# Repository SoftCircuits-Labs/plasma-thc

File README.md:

# plasma-thc
A fully isolated Plasma THC which an be used with any CNC control system which accepts torch Up and Down signals, eg. MACH 3, LinuxCNC, CNConv, Planet CNC etc

The Plasma THC has 2 parts - PTHC-Driver (controller unit) and the PTHC-Probe (for voltage sensing), which are connected via an optical cable.
- PTHC-Probe is installed close to the plasma source. It connects to plasma voltage and runs from a 12VDC supply (provided with the device).
- PTHC-Driver unit is installed closer to the CNC controller. It gives signal to the CNC controller for torch UP, DOWN and ARC OK. It operates via a 12VDC supply (provided with the device)
- These 2 modules are connected via an optical cable which suppresses any high voltage electrical interference, EMI, spikes etc, which are very common in plasma CNC and can damage the
plasma CNC.

Link to user's manual - https://de60002c-e075-4620-9e75-7ffce0da00f8.usrfiles.com/ugd/de6000_ddb20201a9d644779807a9140060d1e7.pdf

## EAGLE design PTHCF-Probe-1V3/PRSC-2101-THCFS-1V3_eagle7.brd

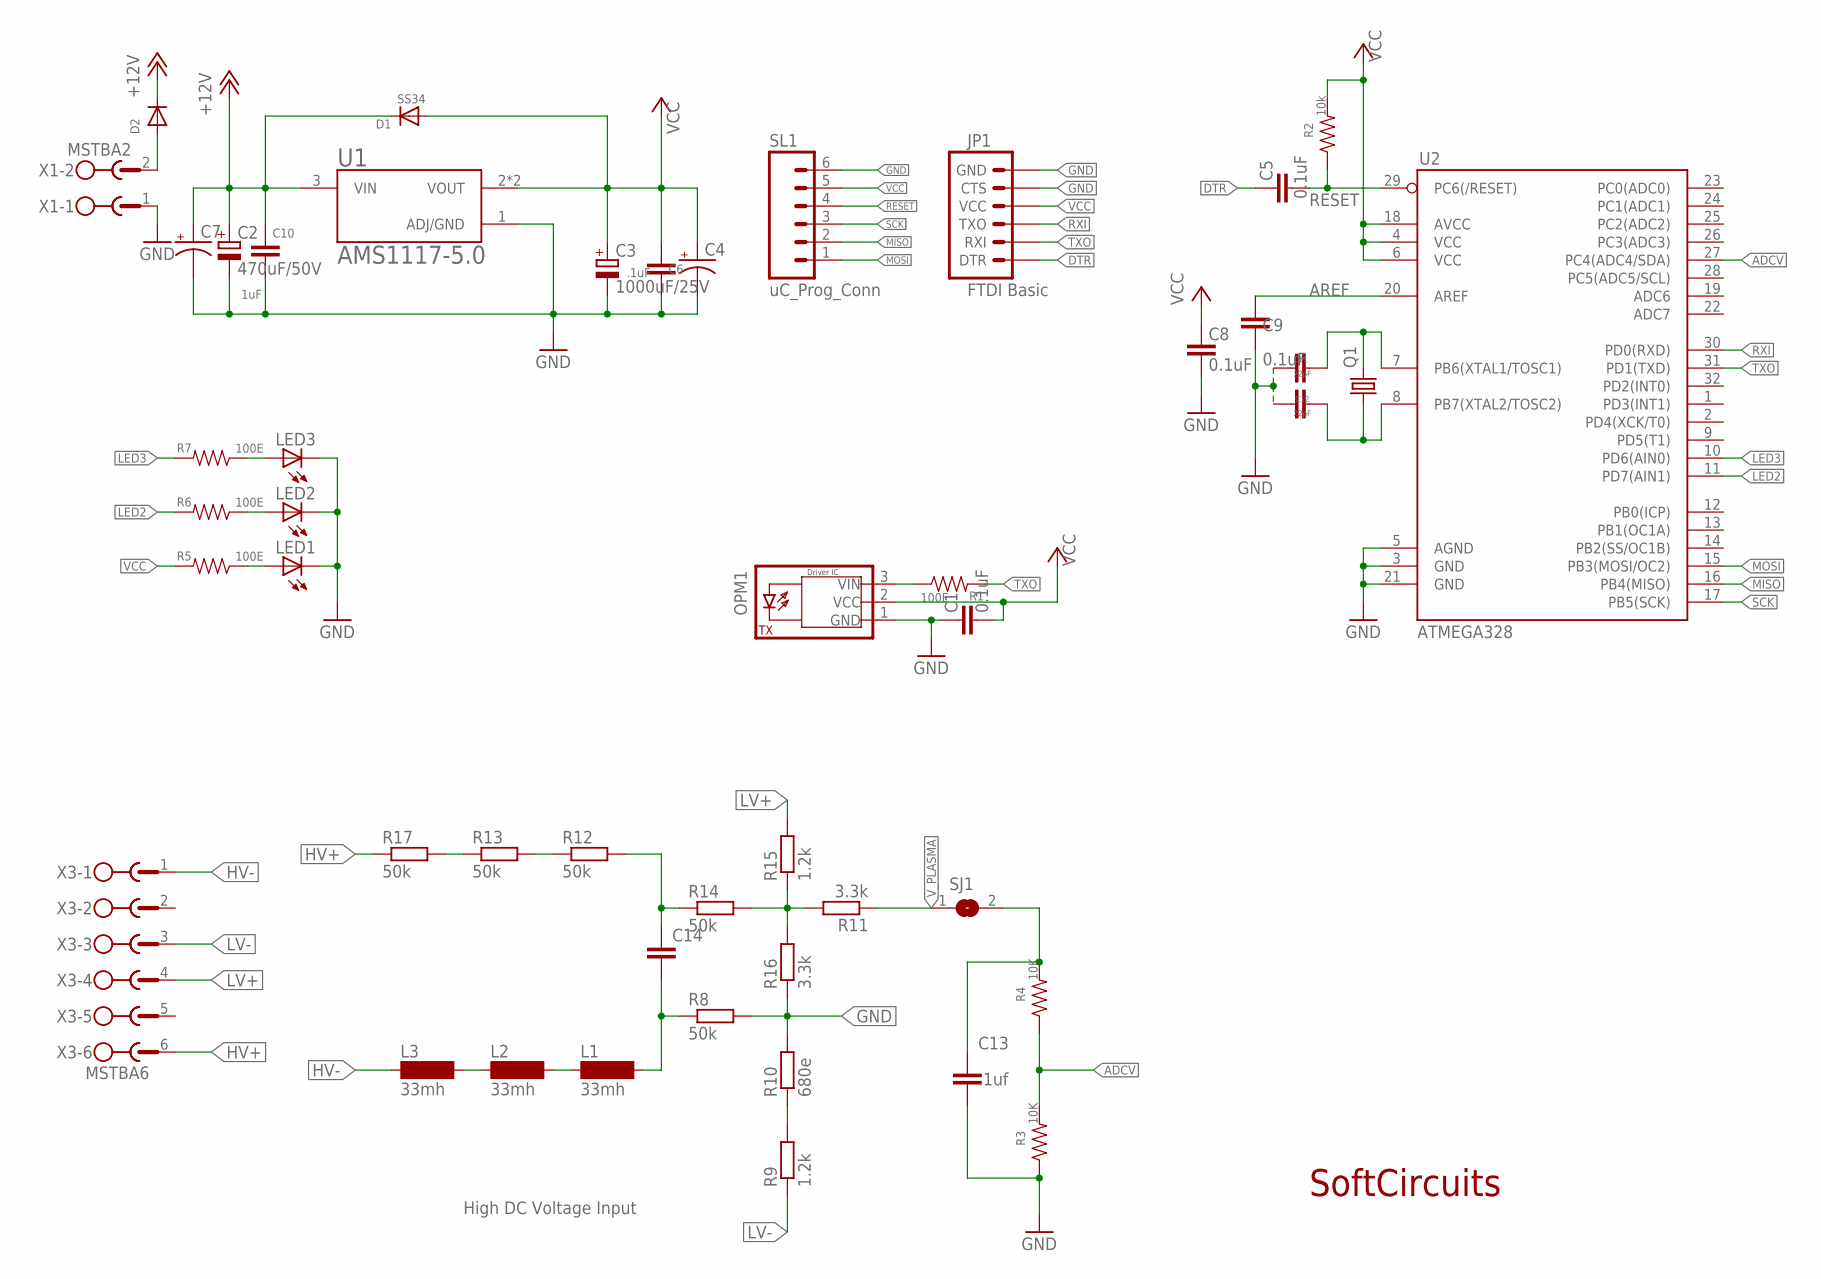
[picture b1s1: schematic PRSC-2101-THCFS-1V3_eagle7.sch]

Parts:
C1, C5, C8, C9: 0.1uF; C1206
C2: 470uF/50V; 153CLV-1010
C3: 1000uF/25V; 153CLV-1010
C4, C7: CAP_POL3528-KIT; EIA3528-KIT
C6: .1uF; C1206
C10: 1uF; C1206
C11, C12: 22pF; C1206
C13: .1uf; C1206
C14: C-EU050-025X075; C050-025X075
D1: SS34; SMADIODE
D2: DIODESMA; SMADIODE
JP1: FTDI Basic; 1X06
L1, L2, L3: 33mh; MY_INDUCTOR
LED1, LED2, LED3: LED3MM
OPM1: TOSLINK_DQT-025; TOSLINK_DQ-025
Q1: CRYSTALHC49UP; HC49UP
R1, R5, R6, R7: 100E; 1206
R2: 10k; 1206
R3, R4: 10K; 1206
R8, R12, R13, R14, R17: 50k; 0207/5V
R9, R15: 1.2k; 0207/2V
R10: 680e; 0207/5V
R11: 3.3k; 0207/2V
R16: 3.3k; 0207/15
SJ1: SJ
SL1: uC_Prog_Conn; 06P
U1: AMS1117-5.0; SOT229P700X180-4N
U2: ATMEGA328; TQFP32-08
X1: MSTBA2
X3: MSTBA6

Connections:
+12V: C2.+, C7.A (+), C10.1, D1.C, D2.C, U1.3 (VIN)
ADCV: R3.2, R4.1, U2.27 (PC4(ADC4/SDA))
AREF: C9.2, U2.20 (AREF)
DTR: C5.2, JP1.1 (DTR)
GND: C1.2, C2.-, C3.-, C4.C (-), C6.2, C7.C (-), C8.1, C9.1, C10.2, C11.2, C12.2, C13.2, JP1.5 (CTS), JP1.6 (GND), LED1.K (C), LED2.K (C), LED3.K (C), OPM1.1 (GND), R3.1, R8.2, R10.2, R16.1, SL1.6, U1.1 (ADJ/GND), U2.3 (GND), U2.5 (AGND), U2.21 (GND), X1.1
HV+: R17.1, X3.6
HV-: L3.1, X3.1
LED2: R6.2, U2.11 (PD7(AIN1))
LED3: R7.2, U2.10 (PD6(AIN0))
LV+: R15.2, X3.4
LV-: R9.1, X3.3
MISO: SL1.2, U2.16 (PB4(MISO))
MOSI: SL1.1, U2.15 (PB3(MOSI/OC2))
unnamed: LED3.A, R7.1
unnamed: R13.1, R17.2
unnamed: C14.1, R12.2, R14.1
unnamed: L1.1, L2.2
unnamed: D2.A, X1.2
unnamed: R12.1, R13.2
unnamed: L2.1, L3.2
unnamed: C14.2, L1.2, R8.1
unnamed: OPM1.3 (VIN), R1.1
unnamed: R11.2, R14.2, R15.1, R16.2
unnamed: C11.1, Q1.2, U2.7 (PB6(XTAL1/TOSC1))
unnamed: R9.2, R10.1
unnamed: C12.1, Q1.1, U2.8 (PB7(XTAL2/TOSC2))
unnamed: LED2.A, R6.1
unnamed: LED1.A, R5.1
PLASMA_VIN: C13.1, R4.2, SJ1.2
RESET: C5.1, R2.1, SL1.4, U2.29 (PC6(/RESET))
RXI: JP1.3 (TXO), U2.30 (PD0(RXD))
SCK: SL1.3, U2.17 (PB5(SCK))
TXO: JP1.2 (RXI), R1.2, U2.31 (PD1(TXD))
VCC: C1.1, C3.+, C4.A (+), C6.1, C8.2, D1.A, JP1.4 (VCC), OPM1.2 (VCC), R2.2, R5.2, SL1.5, U1.2 (VOUT), U1.4 (VOUT), U2.4 (VCC), U2.6 (VCC), U2.18 (AVCC)
V_PLASMA: R11.1, SJ1.1

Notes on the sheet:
SoftCircuits
High DC Voltage Input

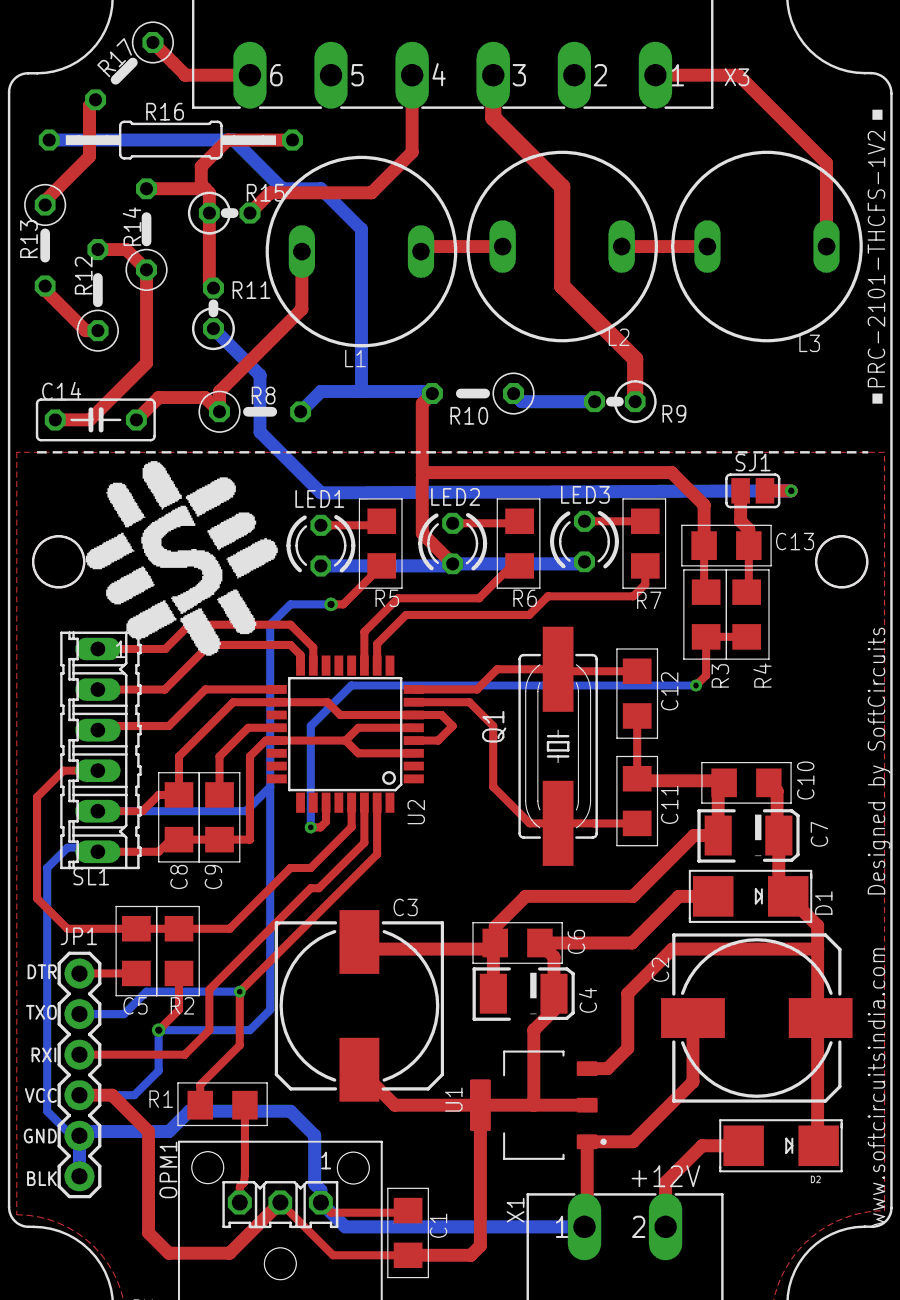
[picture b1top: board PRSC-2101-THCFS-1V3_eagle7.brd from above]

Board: 2 copper layers, 50 parts (1 on the bottom side), 35 nets.

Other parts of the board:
LOGO1, LOGO100: SC_LOGO

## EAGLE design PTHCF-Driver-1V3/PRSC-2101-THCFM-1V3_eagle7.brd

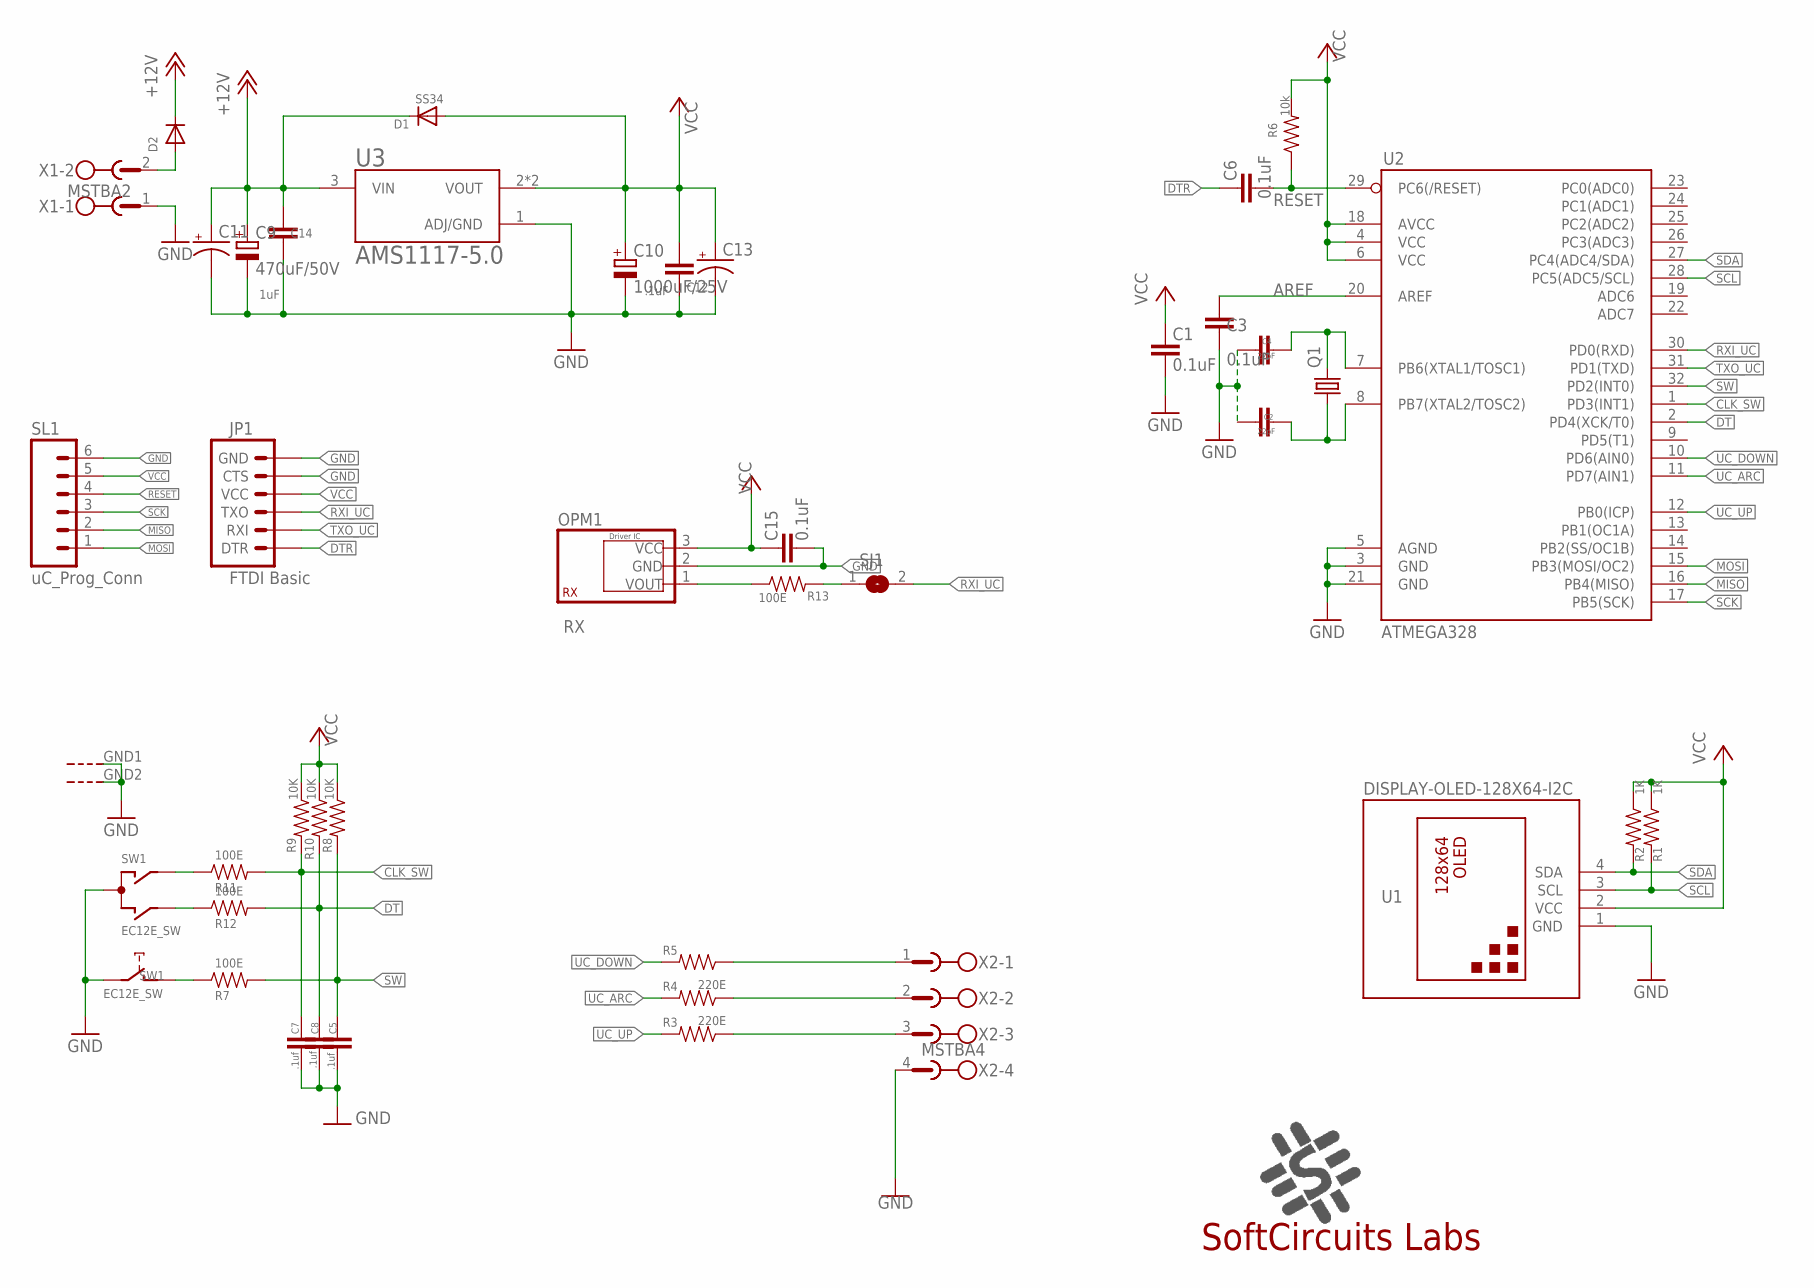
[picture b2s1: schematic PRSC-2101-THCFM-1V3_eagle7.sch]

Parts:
C1, C3, C6, C15: 0.1uF; C1206
C2, C4: 22pF; C1206
C5, C7, C8: .1uf; C1206
C9: 470uF/50V; 153CLV-1010
C10: 1000uF/25V; 153CLV-1010
C11, C13: CAP_POL3528-KIT; EIA3528-KIT
C12: .1uF; 1206
C14: 1uF; 1206
D1: SS34; SMADIODE
D2: DIODESMA; SMADIODE
JP1: FTDI Basic; 1X06
LOGO100: SC_LOGO
OPM1: RX; TOSLINK_DQ-025
Q1: CRYSTALHC49UP; HC49UP
R1, R2: 1K; 1206
R3, R4, R5: 220E; 1206
R6: 10k; 1206
R7, R11, R12, R13: 100E; 1206
R8, R9, R10: 10K; 1206
SJ1: SJ
SL1: uC_Prog_Conn; 06P
SW1: EC12E_SW; ALPS_EC12E_SW
U1: DISPLAY-OLED-128X64-I2C
U2: ATMEGA328; TQFP32-08
U3: AMS1117-5.0; SOT229P700X180-4N
X1: MSTBA2
X2: MSTBA4

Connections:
+12V: C9.+, C11.A (+), C14.1, D1.C, D2.C, U3.3 (VIN)
AREF: C3.2, U2.20 (AREF)
CLK_SW: C7.1, R9.2, R11.2, U2.1 (PD3(INT1))
DT: C8.1, R10.2, R12.2, U2.2 (PD4(XCK/T0))
DTR: C6.2, JP1.1 (DTR)
GND: C1.1, C2.2, C3.1, C4.2, C5.2, C7.2, C8.2, C9.-, C10.-, C11.C (-), C12.2, C13.C (-), C14.2, C15.1, JP1.5 (CTS), JP1.6 (GND), OPM1.2 (GND), SL1.6, SW1.C, SW1.E (2), SW1.GND1 (G), SW1.GND2 (G), U1.1 (GND), U2.3 (GND), U2.5 (AGND), U2.21 (GND), U3.1 (ADJ/GND), X1.1, X2.4
MISO: SL1.2, U2.16 (PB4(MISO))
MOSI: SL1.1, U2.15 (PB3(MOSI/OC2))
unnamed: R13.2, SJ1.1
unnamed: R7.1, SW1.D (1)
unnamed: R12.1, SW1.B
unnamed: R11.1, SW1.A
unnamed: C4.1, Q1.2, U2.7 (PB6(XTAL1/TOSC1))
unnamed: D2.A, X1.2
unnamed: OPM1.1 (VOUT), R13.1
unnamed: C2.1, Q1.1, U2.8 (PB7(XTAL2/TOSC2))
unnamed: R5.1, X2.1
unnamed: R3.1, X2.3
unnamed: R4.1, X2.2
RESET: C6.1, R6.1, SL1.4, U2.29 (PC6(/RESET))
RXI_UC: JP1.3 (TXO), SJ1.2, U2.30 (PD0(RXD))
SCK: SL1.3, U2.17 (PB5(SCK))
SCL: R1.2, U1.3 (SCL), U2.28 (PC5(ADC5/SCL))
SDA: R2.2, U1.4 (SDA), U2.27 (PC4(ADC4/SDA))
SW: C5.1, R7.2, R8.2, U2.32 (PD2(INT0))
TXO_UC: JP1.2 (RXI), U2.31 (PD1(TXD))
UC_ARC: R4.2, U2.11 (PD7(AIN1))
UC_DOWN: R5.2, U2.10 (PD6(AIN0))
UC_UP: R3.2, U2.12 (PB0(ICP))
VCC: C1.2, C10.+, C12.1, C13.A (+), C15.2, D1.A, JP1.4 (VCC), OPM1.3 (VCC), R1.1, R2.1, R6.2, R8.1, R9.1, R10.1, SL1.5, U1.2 (VCC), U2.4 (VCC), U2.6 (VCC), U2.18 (AVCC), U3.2 (VOUT), U3.4 (VOUT)

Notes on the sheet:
SoftCircuits Labs

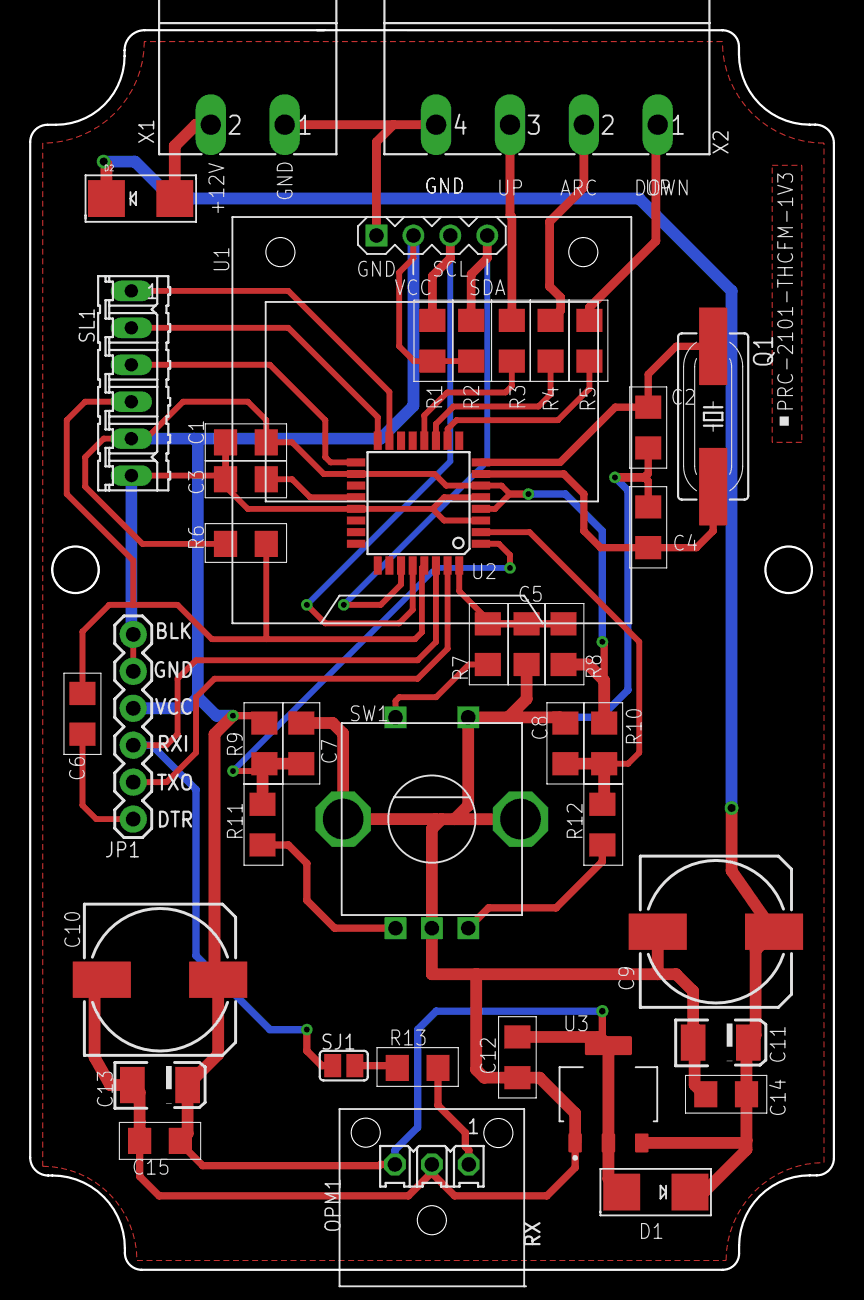
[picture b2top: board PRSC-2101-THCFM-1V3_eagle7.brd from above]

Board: 2 copper layers, 55.3 x 85.2 mm, 42 parts (1 on the bottom side), 30 nets.

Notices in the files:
parts and their libraries:
diy-modules1.8: Released under the Creative Commons Attribution 4.0 International License: http://creativecommons.org/licenses/by/4.0
SoftCircuits-Resistors: Licensing: Creative Commons ShareAlike 4.0 International - https://creativecommons.org/licenses/by-sa/4.0
